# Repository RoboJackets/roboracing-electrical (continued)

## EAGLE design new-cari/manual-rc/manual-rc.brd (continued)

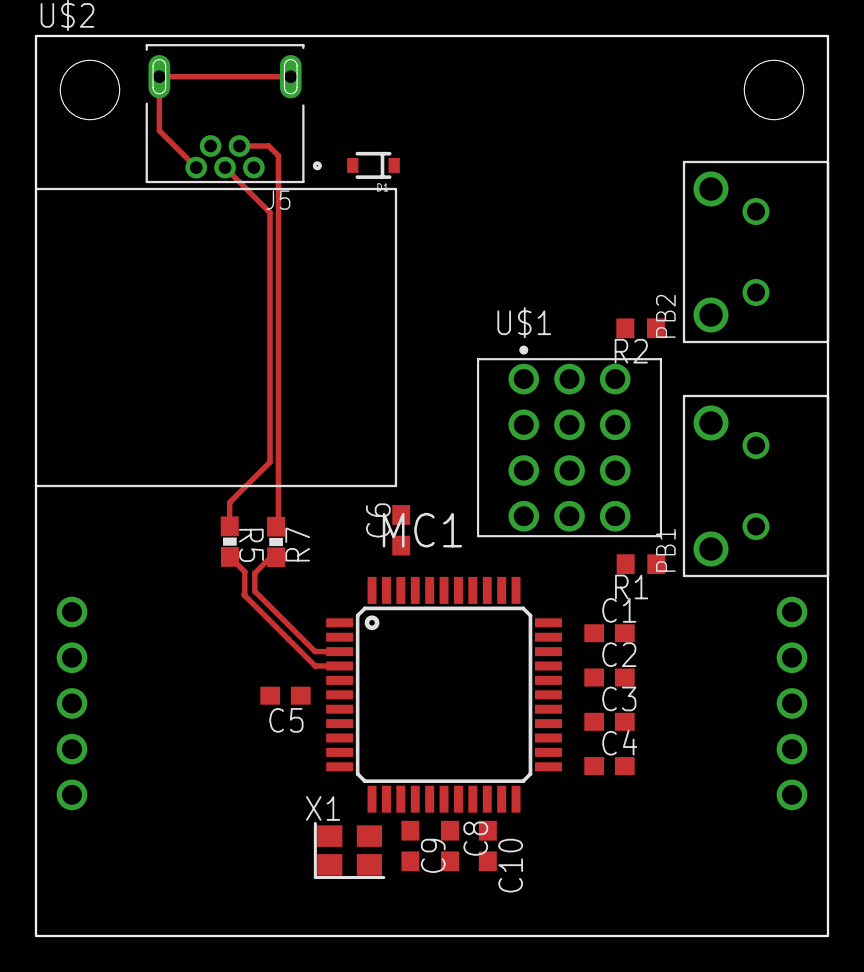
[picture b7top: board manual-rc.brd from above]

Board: 2 copper layers, 44.0 x 50.0 mm, 22 parts (1 on the bottom side), 25 nets.

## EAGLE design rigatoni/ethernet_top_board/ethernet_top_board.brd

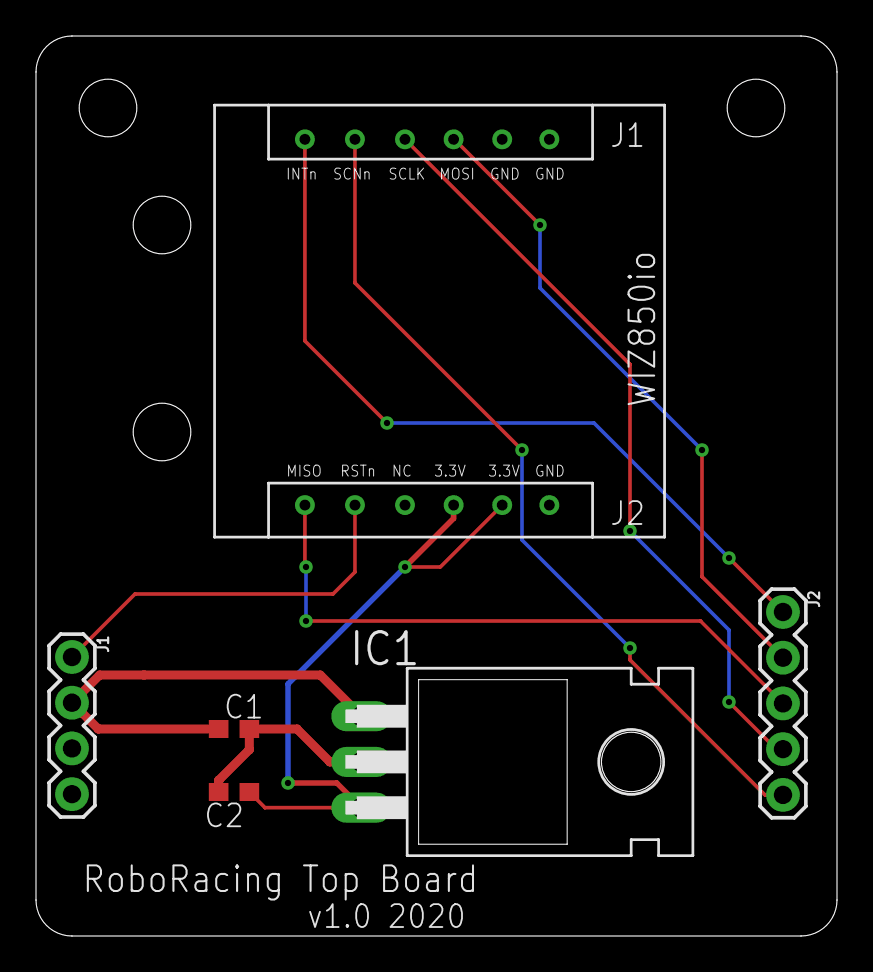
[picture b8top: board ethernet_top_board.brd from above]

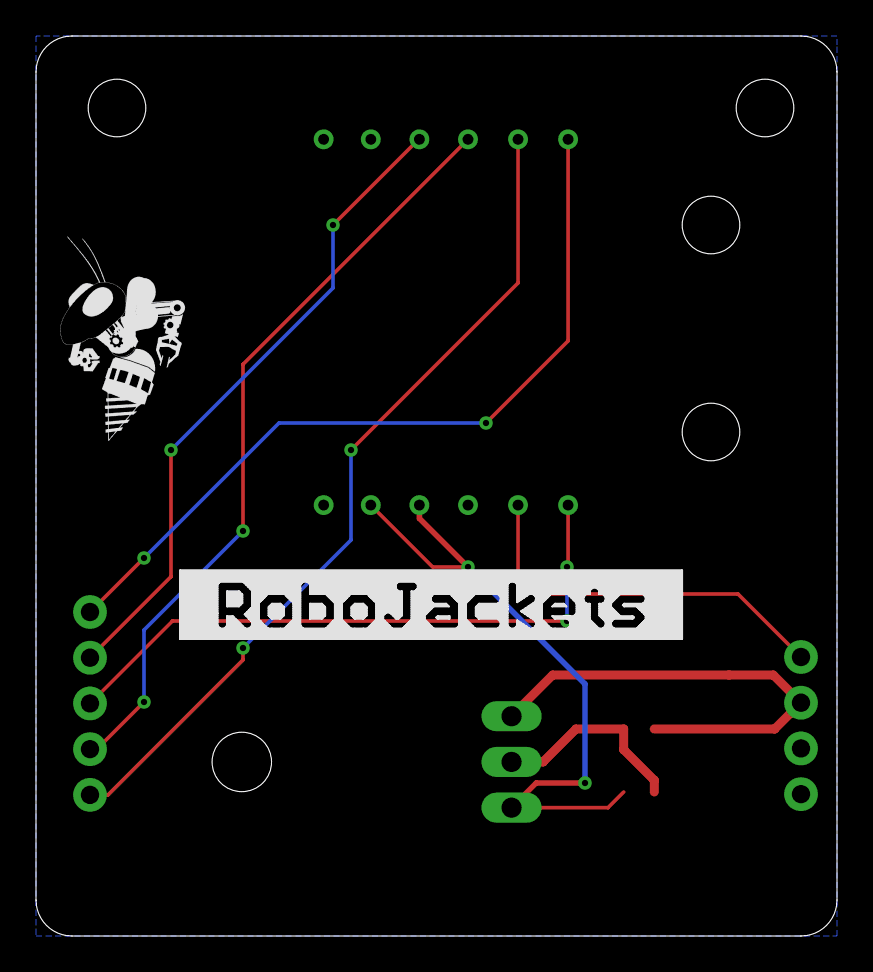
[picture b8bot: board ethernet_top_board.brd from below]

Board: 2 copper layers, 44.5 x 50.0 mm, 8 parts (2 on the bottom side), 9 nets.

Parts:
C1: 0.33 uF; C0603
C2: 0.1 uF; C0603
IC1: LM340H-05; TO220H
J1: 1X04
J2: 1X05
U$1: WIZ850IO
U$2: ROBOBUZZ_0.6X
U$3: ROBOJACKETS

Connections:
!INTN: J2.1, U$1.6
!RSTN: J1.1, U$1.11
+3V3: C2.1, IC1.3, U$1.8, U$1.9
+5V: C1.1, IC1.1, J1.2
GND: C1.2, C2.2, IC1.2, J1.4, U$1.1, U$1.2, U$1.7
MISO: J2.3, U$1.12
MOSI: J2.2, U$1.3
SCLK: J2.4, U$1.4
SCNN: J2.5, U$1.5
